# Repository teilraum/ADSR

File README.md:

# ADSR
LUT based ADSR hosted on an Arduino nano

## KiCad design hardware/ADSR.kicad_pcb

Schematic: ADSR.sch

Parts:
A1: Arduino_Nano_Every; Arduino_Nano
CV_A1: PJ301M-12; Jack_3.5mm_QingPu_WQP-PJ398SM_Vertical_CircularHoles
CV_D1: PJ301M-12; Jack_3.5mm_QingPu_WQP-PJ398SM_Vertical_CircularHoles
CV_R1: PJ301M-12; Jack_3.5mm_QingPu_WQP-PJ398SM_Vertical_CircularHoles
CV_S1: PJ301M-12; Jack_3.5mm_QingPu_WQP-PJ398SM_Vertical_CircularHoles
CV_cA1: PJ301M-12; Jack_3.5mm_QingPu_WQP-PJ398SM_Vertical_CircularHoles
CV_cD1: PJ301M-12; Jack_3.5mm_QingPu_WQP-PJ398SM_Vertical_CircularHoles
CV_cR1: PJ301M-12; Jack_3.5mm_QingPu_WQP-PJ398SM_Vertical_CircularHoles
CV_cS1: PJ301M-12; Jack_3.5mm_QingPu_WQP-PJ398SM_Vertical_CircularHoles
D1, D2, D3: 1N53xxB; D_DO-35_SOD27_P7.62mm_Horizontal
D4: LED; LED_D5.0mm
D5, D6, D7: D; D_DO-35_SOD27_P7.62mm_Horizontal
I_GATE1: PJ301M-12; Jack_3.5mm_QingPu_WQP-PJ398SM_Vertical_CircularHoles
I_RETRIG1: PJ301M-12; Jack_3.5mm_QingPu_WQP-PJ398SM_Vertical_CircularHoles
I_TRIG1: PJ301M-12; Jack_3.5mm_QingPu_WQP-PJ398SM_Vertical_CircularHoles
J1: Conn_02x05_Counter_Clockwise; PinHeader_2x05_P2.54mm_Vertical
OUT+1: PJ301M-12; Jack_3.5mm_QingPu_WQP-PJ398SM_Vertical_CircularHoles
OUT-1: PJ301M-12; Jack_3.5mm_QingPu_WQP-PJ398SM_Vertical_CircularHoles
O_EOA1: PJ301M-12; Jack_3.5mm_QingPu_WQP-PJ398SM_Vertical_CircularHoles
O_EOR1: PJ301M-12; Jack_3.5mm_QingPu_WQP-PJ398SM_Vertical_CircularHoles
P_A1: 100k; Potentiometer_Alps_RK09L_Single_Vertical
P_ACV1: 100k; Potentiometer_Alps_RK09L_Single_Vertical
P_D1: 100k; Potentiometer_Alps_RK09L_Single_Vertical
P_DCV1: 100k; Potentiometer_Alps_RK09L_Single_Vertical
P_R1: 100k; Potentiometer_Alps_RK09L_Single_Vertical
P_RCV1: 100k; Potentiometer_Alps_RK09L_Single_Vertical
P_S1: 100k; Potentiometer_Alps_RK09L_Single_Vertical
P_SCV1: 100k; Potentiometer_Alps_RK09L_Single_Vertical
P_cA1: 100k; Potentiometer_Alps_RK09L_Single_Vertical
P_cACV1: 100k; Potentiometer_Alps_RK09L_Single_Vertical
P_cD1: 100k; Potentiometer_Alps_RK09L_Single_Vertical
P_cDCV1: 100k; Potentiometer_Alps_RK09L_Single_Vertical
P_cR1: 100k; Potentiometer_Alps_RK09L_Single_Vertical
P_cRCV1: 100k; Potentiometer_Alps_RK09L_Single_Vertical
P_cS1: 100k; Potentiometer_Alps_RK09L_Single_Vertical
P_cSCV1: 100k; Potentiometer_Alps_RK09L_Single_Vertical
R1, R3, R5, R7, R9, R10, R11, R12, R13, R14, R15, R17, R19, R21, R23, R24, R25, R26, R28, R32, R33, R34: 100k; R_0805_2012Metric_Pad1.20x1.40mm_HandSolder
R2, R4, R6, R8, R16, R18, R20, R22: 180k; R_0805_2012Metric_Pad1.20x1.40mm_HandSolder
R27: 22k; R_0805_2012Metric_Pad1.20x1.40mm_HandSolder
R29, R30, R31: 200; R_0805_2012Metric_Pad1.20x1.40mm_HandSolder
R35: 1k; R_0805_2012Metric_Pad1.20x1.40mm_HandSolder
R36: 50k; Potentiometer_Trimmer_Bourns_3296W
U1, U3: TLV9004; SOIC-14_3.9x8.7mm_P1.27mm
U2: TL074; SOIC-14_3.9x8.7mm_P1.27mm
U10: MCP4921-EP; SOIC-8-1EP_3.9x4.9mm_P1.27mm_EP2.29x3mm
U11: LM1117-5.0; SOT-223
c1, c2, c3, c4, c5, c8, c9: 100n; C_0805_2012Metric_Pad1.18x1.45mm_HandSolder
c6: 47u; CP_Radial_D5.0mm_P2.50mm
c7: 10n; C_0805_2012Metric_Pad1.18x1.45mm_HandSolder

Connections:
+5V: A1.27 (+5V), R9.2, U1.4, U3.4, U10.1 (VDD), U10.6 (VrefA), U11.2 (VO), c1.1, c2.1, c3.1, c5.1, c8.2, c9.2
+12V: D5.1 (K), U2.4 (V+), U11.3 (VI), c4.1, c6.1
-5V: P_A1.1, P_D1.1, P_R1.1, P_S1.1, P_cA1.1, P_cD1.1, P_cR1.1, P_cS1.1, R14.1, U2.14
-12V: D6.2 (A), U2.11 (V-), c4.2
/A: A1.19 (A0), R10.1, U1.1
/D: A1.20 (A1), R11.1, U1.7
/GATE: A1.10 (D7), D3.1 (K), R31.2
/R: A1.22 (A3), R13.1, U1.14
/S: A1.21 (A2), R12.1, U1.8
/cA: A1.23 (SDA/A4), R23.1, U3.1
/cD: A1.24 (SCL/A5), R24.1, U3.7
/cR: A1.26 (A7), R26.1, U3.14
/cS: A1.25 (A6), R25.1, U3.8
GND: A1.4 (GND), A1.29 (GND), CV_A1.S, CV_A1.TN, CV_D1.S, CV_D1.TN, CV_R1.S, CV_R1.TN, CV_S1.S, CV_S1.TN, CV_cA1.S, CV_cA1.TN, CV_cD1.S, CV_cD1.TN, CV_cR1.S, CV_cR1.TN, CV_cS1.S, CV_cS1.TN, D1.2 (A), D2.2 (A), D3.2 (A), I_GATE1.S, I_RETRIG1.S, I_TRIG1.S, J1.3, J1.4, J1.5, J1.6, J1.7, J1.8, OUT+1.S, OUT-1.S, O_EOA1.S, O_EOR1.S, P_A1.3, P_ACV1.1, P_D1.3, P_DCV1.1, P_R1.3, P_RCV1.1, P_S1.3, P_SCV1.1, P_cA1.3, P_cACV1.1, P_cD1.3, P_cDCV1.1, P_cR1.3, P_cRCV1.1, P_cS1.3, P_cSCV1.1, R32.1, U1.3, U1.5, U1.10, U1.11, U1.12, U2.5 (+), U2.10 (+), U2.12 (+), U3.3, U3.5, U3.10, U3.11, U3.12, U10.7 (AVSS), U11.1 (GND), c1.2, c2.2, c3.2, c5.2, c6.2, c7.2, c8.1, c9.1
unnamed: A1.5 (D2), D1.1 (K), R29.2
unnamed: A1.6 (D3), D2.1 (K), R30.2
unnamed: A1.7 (D4), U10.4 (SDI)
unnamed: A1.8 (D5), U10.3 (SCK)
unnamed: A1.9 (D6), U10.2 (~CS~)
unnamed: A1.11 (D8), U10.5 (~LDAC~)
unnamed: A1.12 (D9), O_EOR1.T
unnamed: A1.13 (D10), O_EOA1.T
unnamed: CV_A1.T, P_ACV1.3
unnamed: CV_D1.T, P_DCV1.3
unnamed: CV_R1.T, P_RCV1.3
unnamed: CV_S1.T, P_SCV1.3
unnamed: CV_cA1.T, P_cACV1.3
unnamed: CV_cD1.T, P_cDCV1.3
unnamed: CV_cR1.T, P_cRCV1.3
unnamed: CV_cS1.T, P_cSCV1.3
unnamed: D4.1 (K), D7.2 (A), U2.8
unnamed: D4.2 (A), D7.1 (K), R35.1, U2.9 (-)
unnamed: D5.2 (A), J1.1, J1.2
unnamed: D6.1 (K), J1.9, J1.10
unnamed: I_GATE1.T, R31.1
unnamed: I_RETRIG1.T, R30.1
unnamed: I_TRIG1.T, R29.1
unnamed: OUT+1.T, R28.2, R34.1, R35.2, U2.1
unnamed: OUT-1.T, R33.1, U2.7
unnamed: P_A1.2, R1.2
unnamed: P_ACV1.2, R2.2
unnamed: P_D1.2, R3.2
unnamed: P_DCV1.2, R4.2
unnamed: P_R1.2, R7.2
unnamed: P_RCV1.2, R8.2
unnamed: P_S1.2, R5.2
unnamed: P_SCV1.2, R6.2
unnamed: P_cA1.2, R15.2
unnamed: P_cACV1.2, R16.2
unnamed: P_cD1.2, R17.2
unnamed: P_cDCV1.2, R18.2
unnamed: P_cR1.2, R21.2
unnamed: P_cRCV1.2, R22.2
unnamed: P_cS1.2, R19.2
unnamed: P_cSCV1.2, R20.2
unnamed: R1.1, R2.1, R10.2, U1.2
unnamed: R3.1, R4.1, R11.2, U1.6
unnamed: R5.1, R6.1, R12.2, U1.9
unnamed: R7.1, R8.1, R13.2, U1.13
unnamed: R9.1, R14.2, U2.13 (-)
unnamed: R15.1, R16.1, R23.2, U3.2
unnamed: R17.1, R18.1, R24.2, U3.6
unnamed: R19.1, R20.1, R25.2, U3.9
unnamed: R21.1, R22.1, R26.2, U3.13
unnamed: R27.1, R36.2, U2.3 (+), c7.1
unnamed: R27.2, R36.1, U10.8 (VoutA)
unnamed: R28.1, R33.2, U2.6 (-)
unnamed: R32.2, R34.2, U2.2 (-)

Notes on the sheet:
[-10; 10] V
[0; 10] V
[0; -10] V
outLED
POWER
INPUT

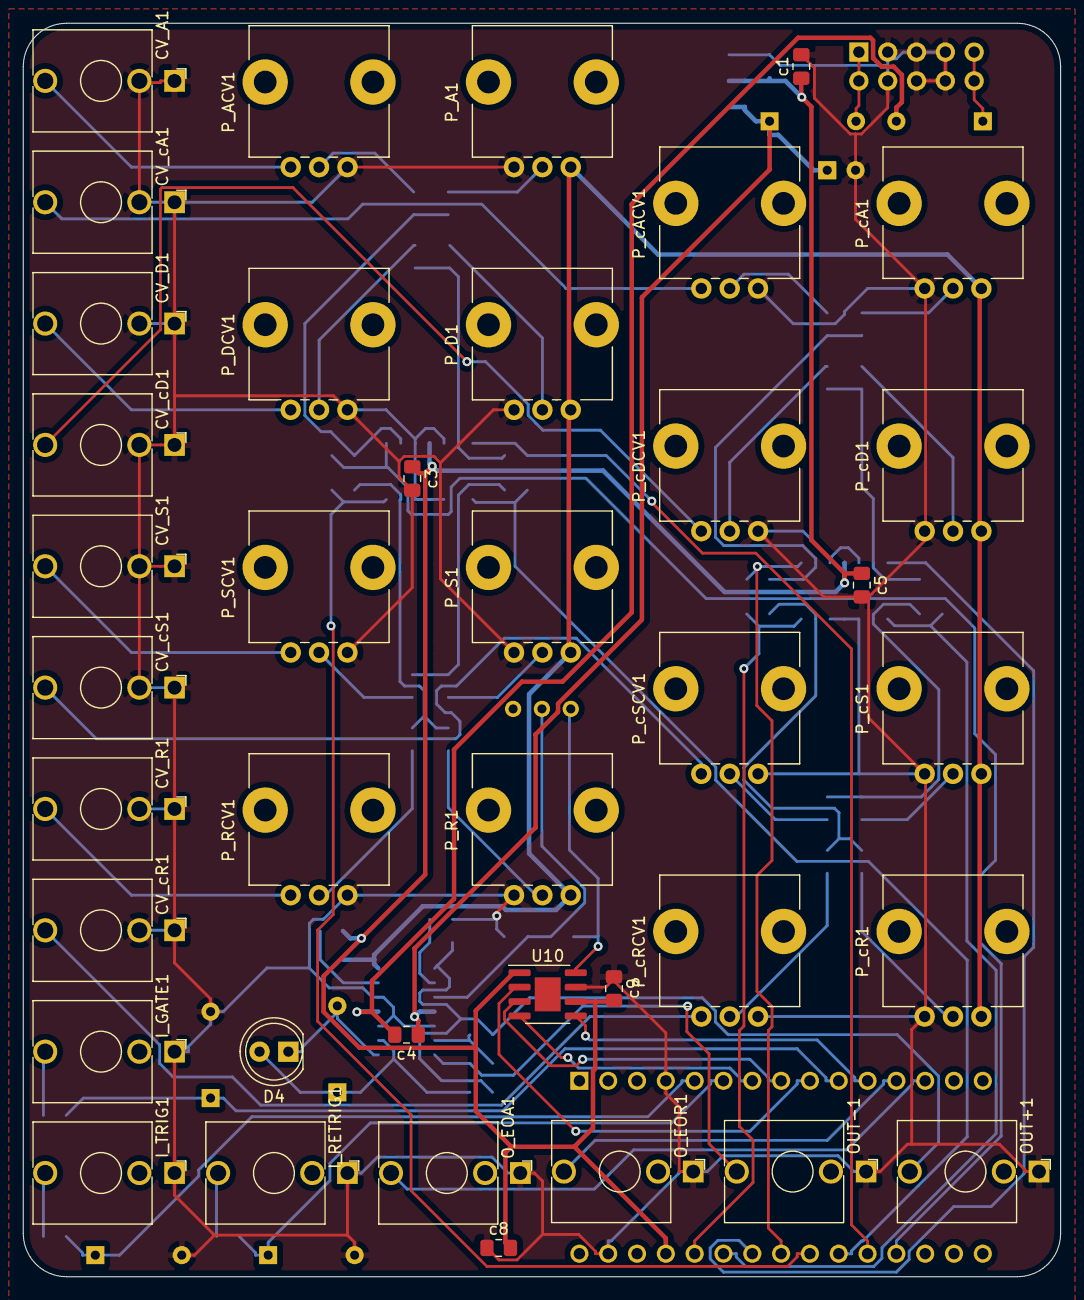
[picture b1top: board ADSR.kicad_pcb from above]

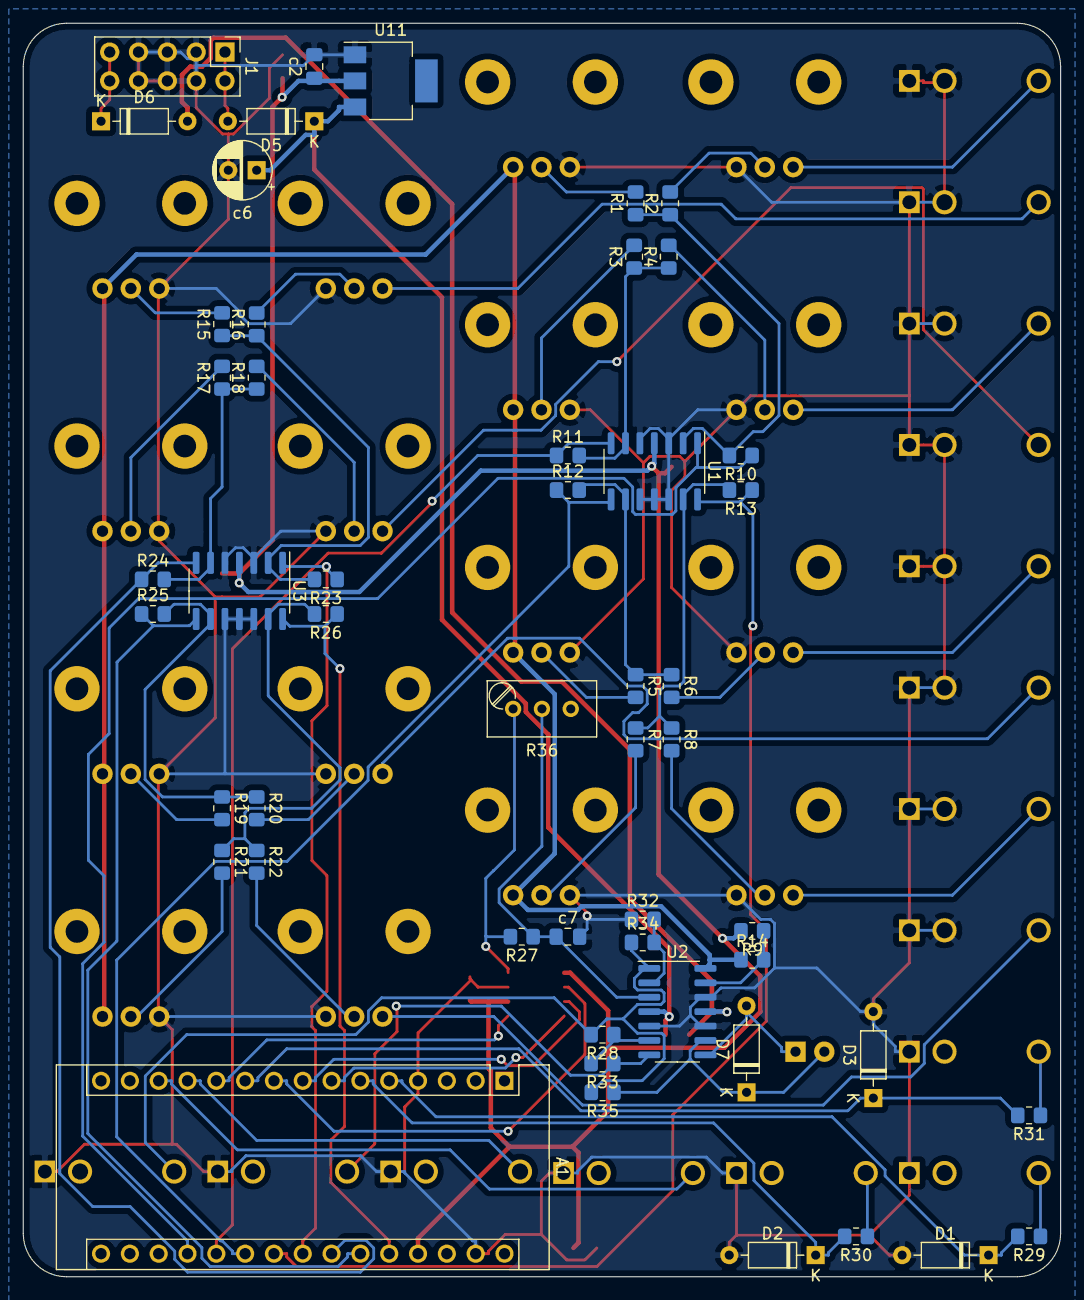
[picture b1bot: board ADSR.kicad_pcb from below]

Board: 2 copper layers, 91.4 x 110.5 mm, 90 parts (51 on the bottom side), 68 nets.

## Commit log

2021-03-15 init
2021-03-15 oved LUT to flash memory
2021-03-15 LUT in flash
2021-03-15 hardware init
2021-03-16 schematic done
2021-03-17 initial PCB layout
2021-03-17 pointers pointers
2021-03-17 renamed schematic
2021-03-17 added TLV9004 to library and placement is final
2021-03-17 added more puffer caps. im lazy. go autoRoute
2021-03-17 front panel layout
2021-03-20 hardware done
2021-03-22 klirrfaktoren logo
